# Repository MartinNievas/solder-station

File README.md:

# Solder Station

En este repositorio se encuentran los códigos y circuitos para fabricar una estación de soldado.

## Requerimientos

### Hardware
  - Arduino pro-mini
  - Punta de soldador Hakko 207 (repuesto) 
  - Fuente 12V@10A
### Software
  - Para compilar y cargar al arduino [platformio](http://platformio.org/).

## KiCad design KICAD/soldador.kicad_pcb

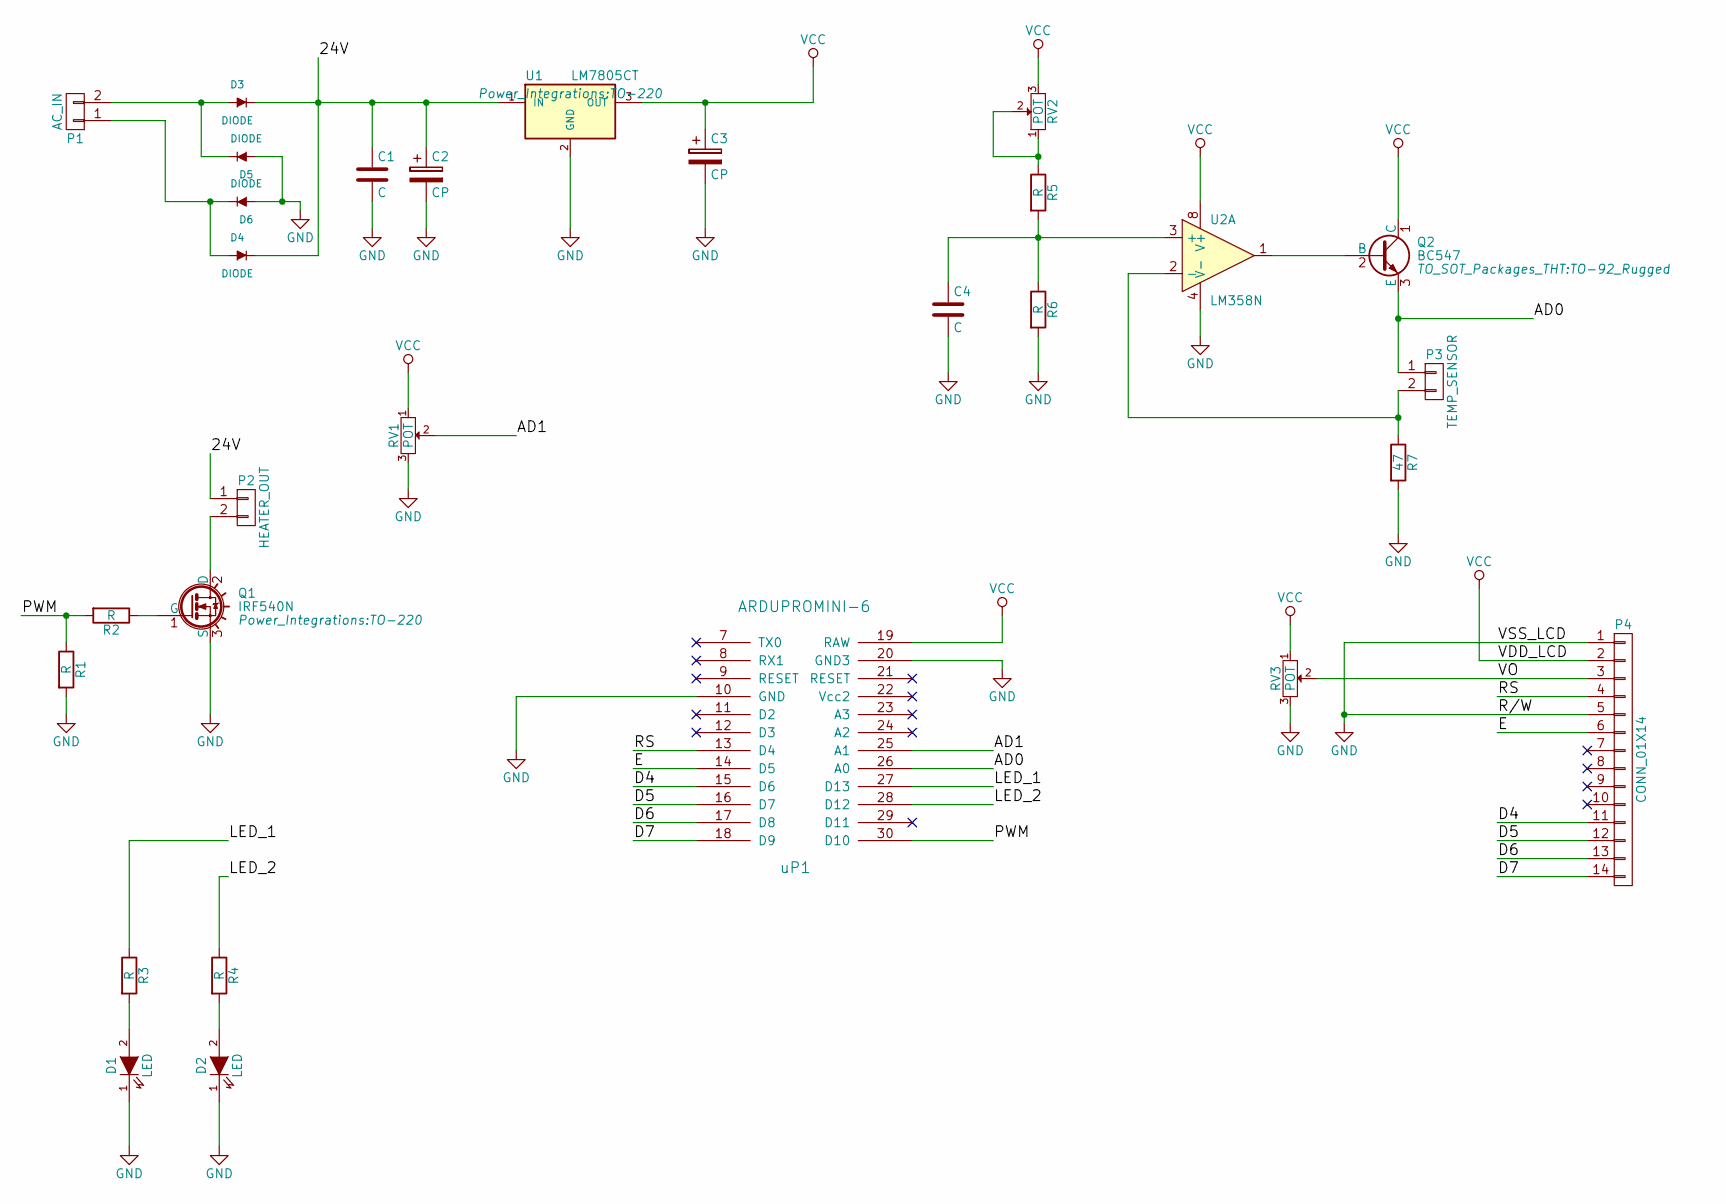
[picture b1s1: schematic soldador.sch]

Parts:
C1, C4: C; C_Disc_D6_P5
C2: CP; C_Radial_D16_L25_P7.5
C3: CP; C_Radial_D8_L11.5_P3.5
D1, D2: LED; LED-5MM
D3, D4, D5, D6: DIODE; Diode_DO-41_SOD81_Horizontal_RM10
P1: AC_IN; Pin_Header_Straight_1x02
P2: HEATER_OUT; Pin_Header_Straight_1x02
P3: TEMP_SENSOR; Pin_Header_Straight_1x02
P4: CONN_01X14; Pin_Header_Straight_1x14
Q1: IRF540N; TO-220
Q2: BC547; TO-92_Rugged
R1, R2, R3, R4, R5, R6: R; Resistor_Horizontal_RM10mm
R7: 47; Resistor_Horizontal_RM10mm
RV1, RV2, RV3: POT; Potentiometer_WirePads_largePads
U1: LM7805CT; TO-220
U2: LM358N; DIP-8_W7.62mm_LongPads
uP1: ARDUPROMINI-6; ArduProMini-6

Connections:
/24V: C1.1, C2.1, D3.2 (K), D4.2 (K), P2.1, U1.1 (IN)
/AD0: P3.1, Q2.3 (E), uP1.26 (A0)
/AD1: RV1.2, uP1.25 (A1)
/D4: P4.11, uP1.15 (D6)
/D5: P4.12, uP1.16 (D7)
/D6: P4.13, uP1.17 (D8)
/D7: P4.14, uP1.18 (D9)
/E: P4.6, uP1.14 (D5)
/LED_1: R3.1, uP1.27 (D13)
/LED_2: R4.1, uP1.28 (D12)
/PWM: R1.1, R2.2, uP1.30 (D10)
/RS: P4.4, uP1.13 (D4)
/VO: P4.3, RV3.2
GND: C1.2, C2.2, C3.2, C4.2, D1.1 (K), D2.1 (K), D5.1 (A), D6.1 (A), P4.1, P4.5, Q1.3 (S), R1.2, R6.2, R7.2, RV1.3, RV3.3, U1.2 (GND), U2.4 (V-), uP1.10 (GND), uP1.20 (GND3); also elsewhere on the board
unnamed: C4.1, R5.2, R6.1, U2.3 (+)
unnamed: D1.2 (A), R3.2
unnamed: D2.2 (A), R4.2
unnamed: D3.1 (A), D5.2 (K), P1.2
unnamed: D4.1 (A), D6.2 (K), P1.1
unnamed: P2.2, Q1.2 (D)
unnamed: P3.2, R7.1, U2.2 (-)
unnamed: Q1.1 (G), R2.1
unnamed: Q2.2 (B), U2.1
unnamed: R5.1, RV2.1, RV2.2
VCC: C3.1, P4.2, Q2.1 (C), RV1.1, RV2.3, RV3.1, U1.3 (OUT), U2.8 (V+), uP1.19 (RAW)

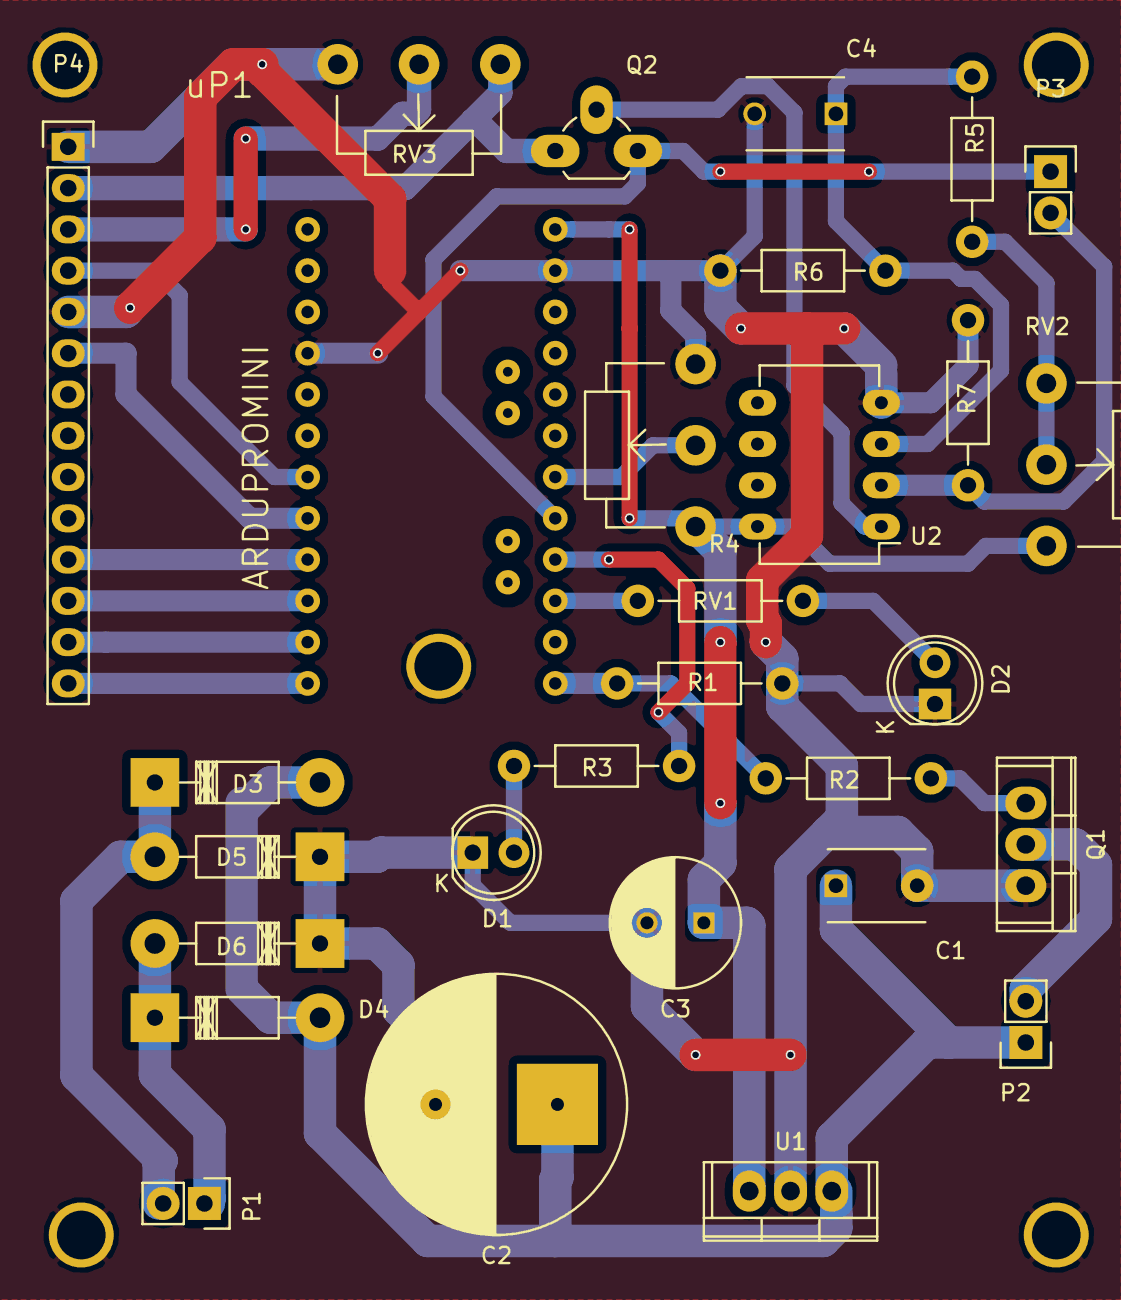
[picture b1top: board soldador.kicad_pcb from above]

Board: 2 copper layers, 34 parts (0 on the bottom side), 25 nets.

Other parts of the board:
 : #; SolderWirePad_single_2mmDrill
 #2,  #3,  #4,  #5: #; SolderWirePad_single_2mmDrill

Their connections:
GND: ., #2., #3., #4., #5.; also elsewhere on the board

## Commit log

2017-09-28 Electrónica. Circuitos y esquemáticos
2017-09-28 código para arduino pro-mini
2017-09-28 README
2020-03-13 Agrega pdf del esquemático
2020-03-13 Ordena archivos
